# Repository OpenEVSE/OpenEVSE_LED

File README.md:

# OpenEVSE_LED
OpenEVSE Light Emitting Diode (LED)

OpenEVSE_LED Original version

OpenEVSE_LED_v2 Adds MCP9808 Temperature Sensor

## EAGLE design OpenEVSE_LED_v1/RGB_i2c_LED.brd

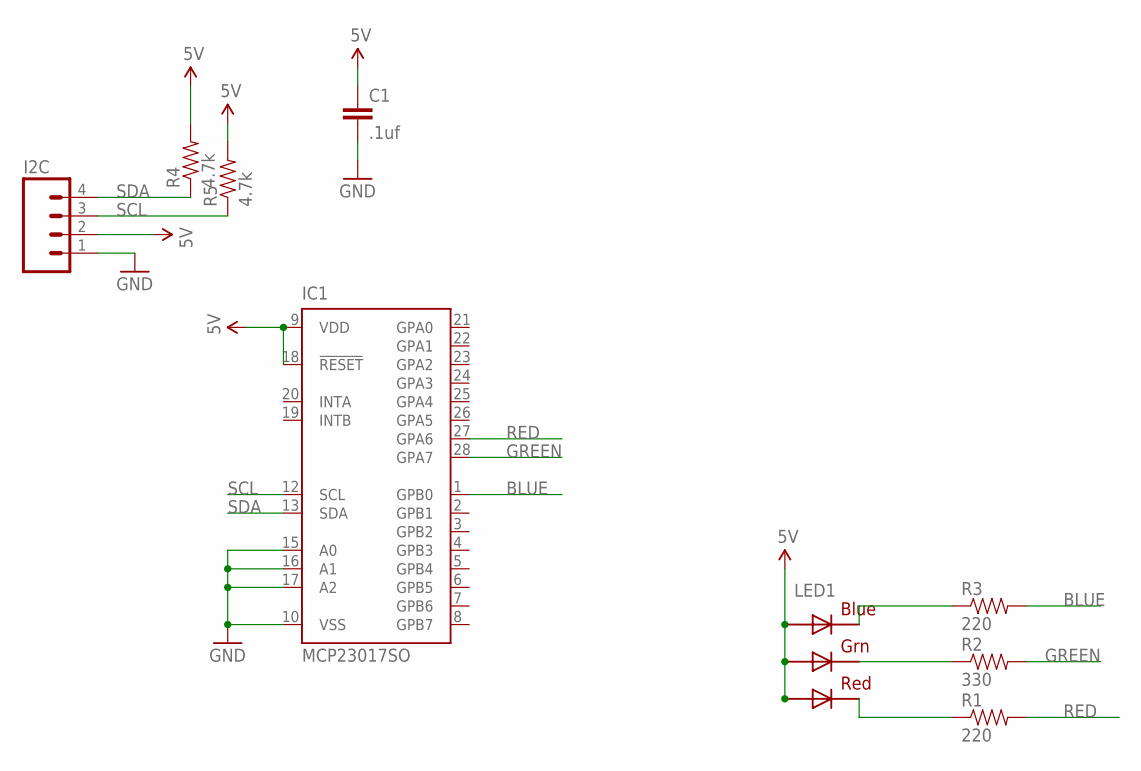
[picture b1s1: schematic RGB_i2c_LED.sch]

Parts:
C1: .1uf; 0805
I2C: M04LOCK; 1X04_LOCK
IC1: MCP23017SO; SO28W
LED1: RGBLED5050
R1, R3: 220; 0805
R2: 330; 0805
R4, R5: 4.7k; 0805

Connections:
5V: C1.1, I2C.2, IC1.9 (VDD), IC1.18 (!RESET), LED1.4 (GREEN_A), LED1.5 (RED_A), LED1.6 (BLUE_A), R4.2, R5.2
BLUE: IC1.1 (GPB0), R3.2
GND: C1.2, I2C.1, IC1.10 (VSS), IC1.15 (A0), IC1.16 (A1), IC1.17 (A2)
GREEN: IC1.28 (GPA7), R2.2
unnamed: LED1.1 (GREEN_C), R2.1
unnamed: LED1.2 (RED_C), R1.1
unnamed: LED1.3 (BLUE_C), R3.1
RED: IC1.27 (GPA6), R1.2
SCL: I2C.3, IC1.12 (SCL), R5.1
SDA: I2C.4, IC1.13 (SDA), R4.1

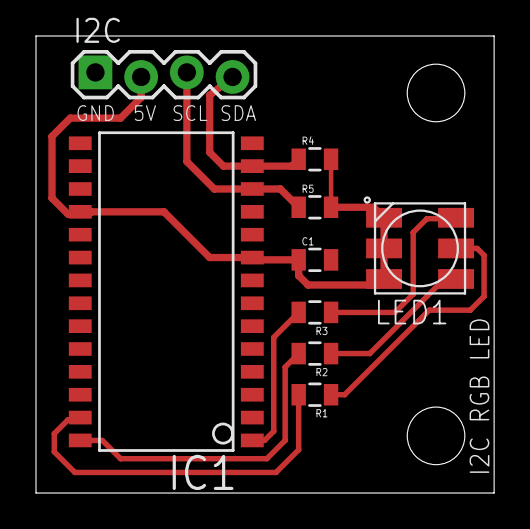
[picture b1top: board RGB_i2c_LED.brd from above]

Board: 2 copper layers, 25.5 x 25.4 mm, 9 parts (0 on the bottom side), 10 nets.

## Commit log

2015-10-09 :lollipop: Added .gitattributes & .gitignore files
2015-10-09 OpenEVSE_LED
    OpenEVSE Light Emitting Diode
